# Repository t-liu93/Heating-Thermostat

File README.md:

# ESP8266-Relay

This project is aiming at making a wireless relay module which can be used for central-heating boiler.

## Before first time use
Install necessary packages:
```bash
sudo apt-get update
sudo apt-get install libconfig-yaml-perl unzip sed
```

## After cloning the repository
```bash
cd extern/Arduino/tools && ./get.py
```

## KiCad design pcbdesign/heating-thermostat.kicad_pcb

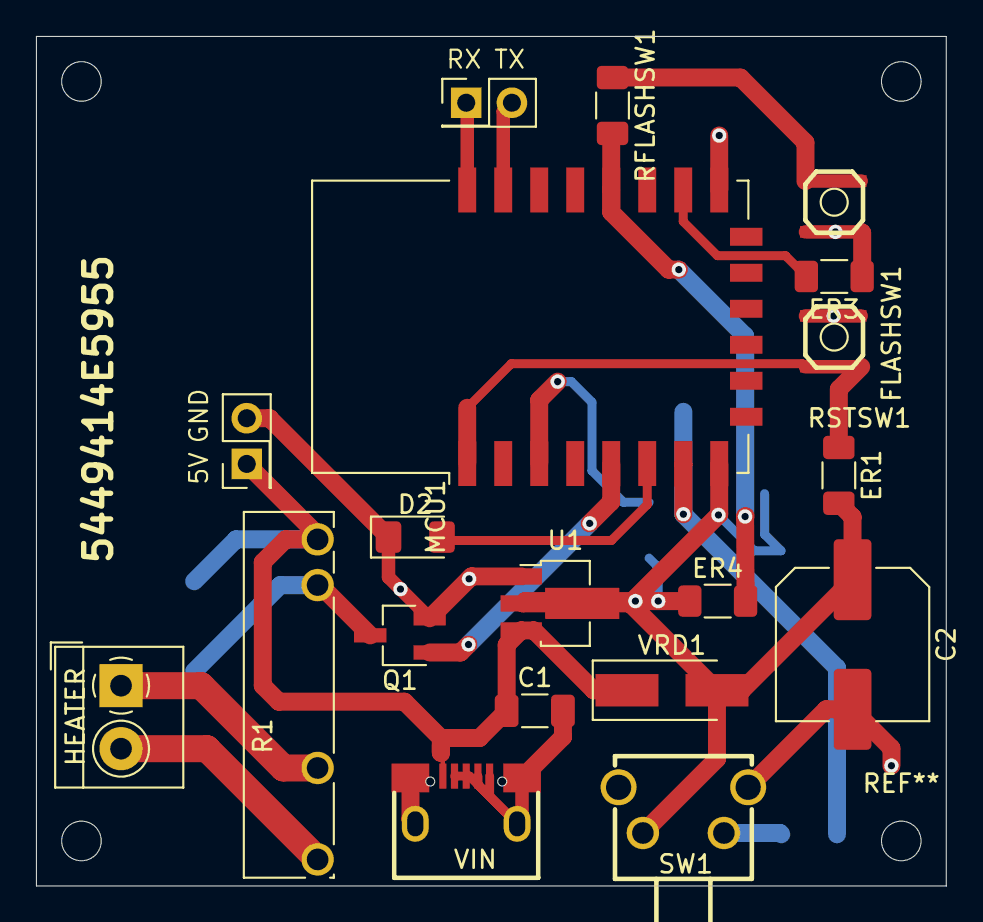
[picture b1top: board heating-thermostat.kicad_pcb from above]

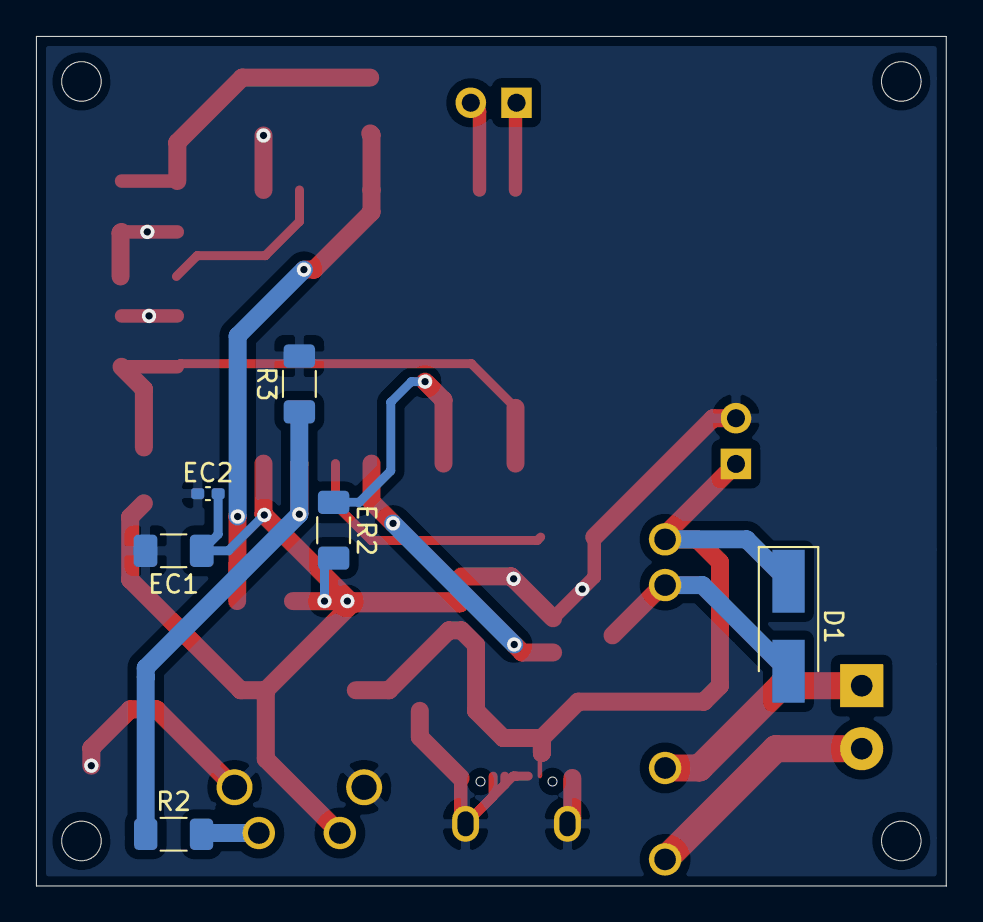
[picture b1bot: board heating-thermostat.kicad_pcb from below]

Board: 2 copper layers, 50.5 x 47.2 mm, 23 parts (6 on the bottom side), 15 nets.

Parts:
C1: 10uF; C_1206_3216Metric_Pad1.33x1.80mm_HandSolder
C2: 100uF; C_Elec_8x10.2
D1: D_Schottky; D_SMA_Handsoldering
D2: LED; D_1206_3216Metric_Pad1.42x1.75mm_HandSolder
EC1: 10uF; C_1206_3216Metric_Pad1.33x1.80mm_HandSolder
EC2: 100nF; C_0402_1005Metric_Pad0.74x0.62mm_HandSolder
ER1, ER2, ER3, ER4: 10K; R_1206_3216Metric_Pad1.30x1.75mm_HandSolder
FLASHSW1: SW_MEC_5E; SW-SMD_4P_KAN3742-035B020
HEATER: TerminalBlock_4Ucon_1x02_P3.50mm_Horizontal
MCU1: ESP-12F; ESP-12E
Q1: DTC124E; SC-59_Handsoldering
R1: Relay_THT_HF49FD
R2: 100; R_1206_3216Metric_Pad1.30x1.75mm_HandSolder
R3: 10K; R_1206_3216Metric_Pad1.30x1.75mm_HandSolder
RFLASHSW1: 100; R_1206_3216Metric_Pad1.30x1.75mm_HandSolder
RSTSW1: SW_MEC_5E; SW-SMD_4P_KAN3742-035B020
SW1: SW_Push; KEY-TH_K2-1102AQ-K4CW-01
U1: LM1117-3.3; SOT-89-3_Handsoldering
VIN: MICRO-USB-SMD_U254-051T-4BH83-F1S
VRD1: D_Schottky; D_SMA_Handsoldering

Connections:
+3V3: C2.1, EC1.1, EC2.2, ER1.2, ER2.2, ER4.1, MCU1.8, SW1.1, U1.2, VRD1.2
+5V: C1.1, D1.1, R1.1, U1.3, VIN.1, VRD1.1
/BTN: MCU1.7, R2.1, R3.1
/ESP12F/EN: ER2.1, MCU1.3
/ESP12F/GPIO0: ER4.2, MCU1.18, RFLASHSW1.2
/ESP12F/GPIO15: ER3.2, MCU1.16
/ESP12F/RST: ER1.1, MCU1.1, RSTSW1.3, RSTSW1.4
/OUT1: HEATER.1, R1.3
/OUT2: HEATER.2, R1.4
/RELAY: MCU1.5, Q1.1
/STATUS: D2.2, MCU1.6
GND: C1.2, C2.2, D2.1, EC1.2, EC2.1, ER3.1, FLASHSW1.3, FLASHSW1.4, MCU1.15, Q1.2, R3.2, RSTSW1.1, RSTSW1.2, SW1.3, SW1.4, U1.1, VIN.2, VIN.3, VIN.4, VIN.5, VIN.6, VIN.7, VIN.8, VIN.9
unnamed: D1.2, Q1.3, R1.2
unnamed: FLASHSW1.1, FLASHSW1.2, RFLASHSW1.1
unnamed: R2.2, SW1.2

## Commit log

2019-11-23 Update first readme.
2019-11-23 Add LICENSE
2019-11-23 Add .gitignore
2019-11-23 Modify .gitignore now ignore vscode files.
2019-11-23 Add first version of WIFI module
2019-11-24 Redesign file structure to adhere to Arduino IDE
2019-11-24 Rename the library ino file to cpp to solve linking issues.
2019-11-24 Add test for getting mqtt payload
2019-11-24 WIP, successfully control relay
2019-11-25 Add temp extractor, WIP, temp working
2019-12-24 Working example
2019-12-25 Add led controlling module, currently only two types of blinking
2019-12-25 First working version with error handling
2019-12-25 Clean up print statements
2019-12-25 Use debug flag to change print statements
2019-12-26 Add pubsubclient as submodule
2019-12-26 Add esp8266 makefile as submodule
2019-12-26 Add esp8266 as submodule
2019-12-27 Rename relay.ino to corresponding folder name
2019-12-27 Rename src folder to libraries folder
2019-12-27 Update .gitignore to ignore all build folder start with build
2019-12-27 Add Makefile
2019-12-27 Move helper.h out
2019-12-27 Restructure lib
2019-12-27 Fix bug in Makefile
2019-12-27 Remove defines in code
2019-12-27 Remove wifi password printing
2019-12-27 Change LED defines
2019-12-27 Rename
2019-12-27 Update include define
2019-12-27 Update a include in ino file
2019-12-28 Add CHANGELOG v0.1
2019-12-28 Update CHANGELOG
2020-02-17 Update readme for first time use
2020-02-17 Bump Arduino extern
2020-02-17 Bump ESP8266 Arduino Makefile
2020-10-24 Move to software
2020-10-24 Add submodule
2020-11-19 Add pcbdesign
2020-12-05 Remove submodule
2020-12-05 Remove all
2020-12-05 Update ignore
2020-12-05 Add basic control
2020-12-06 Start with mqtt
2020-12-07 Finished software implementation
2020-12-24 Update sw
